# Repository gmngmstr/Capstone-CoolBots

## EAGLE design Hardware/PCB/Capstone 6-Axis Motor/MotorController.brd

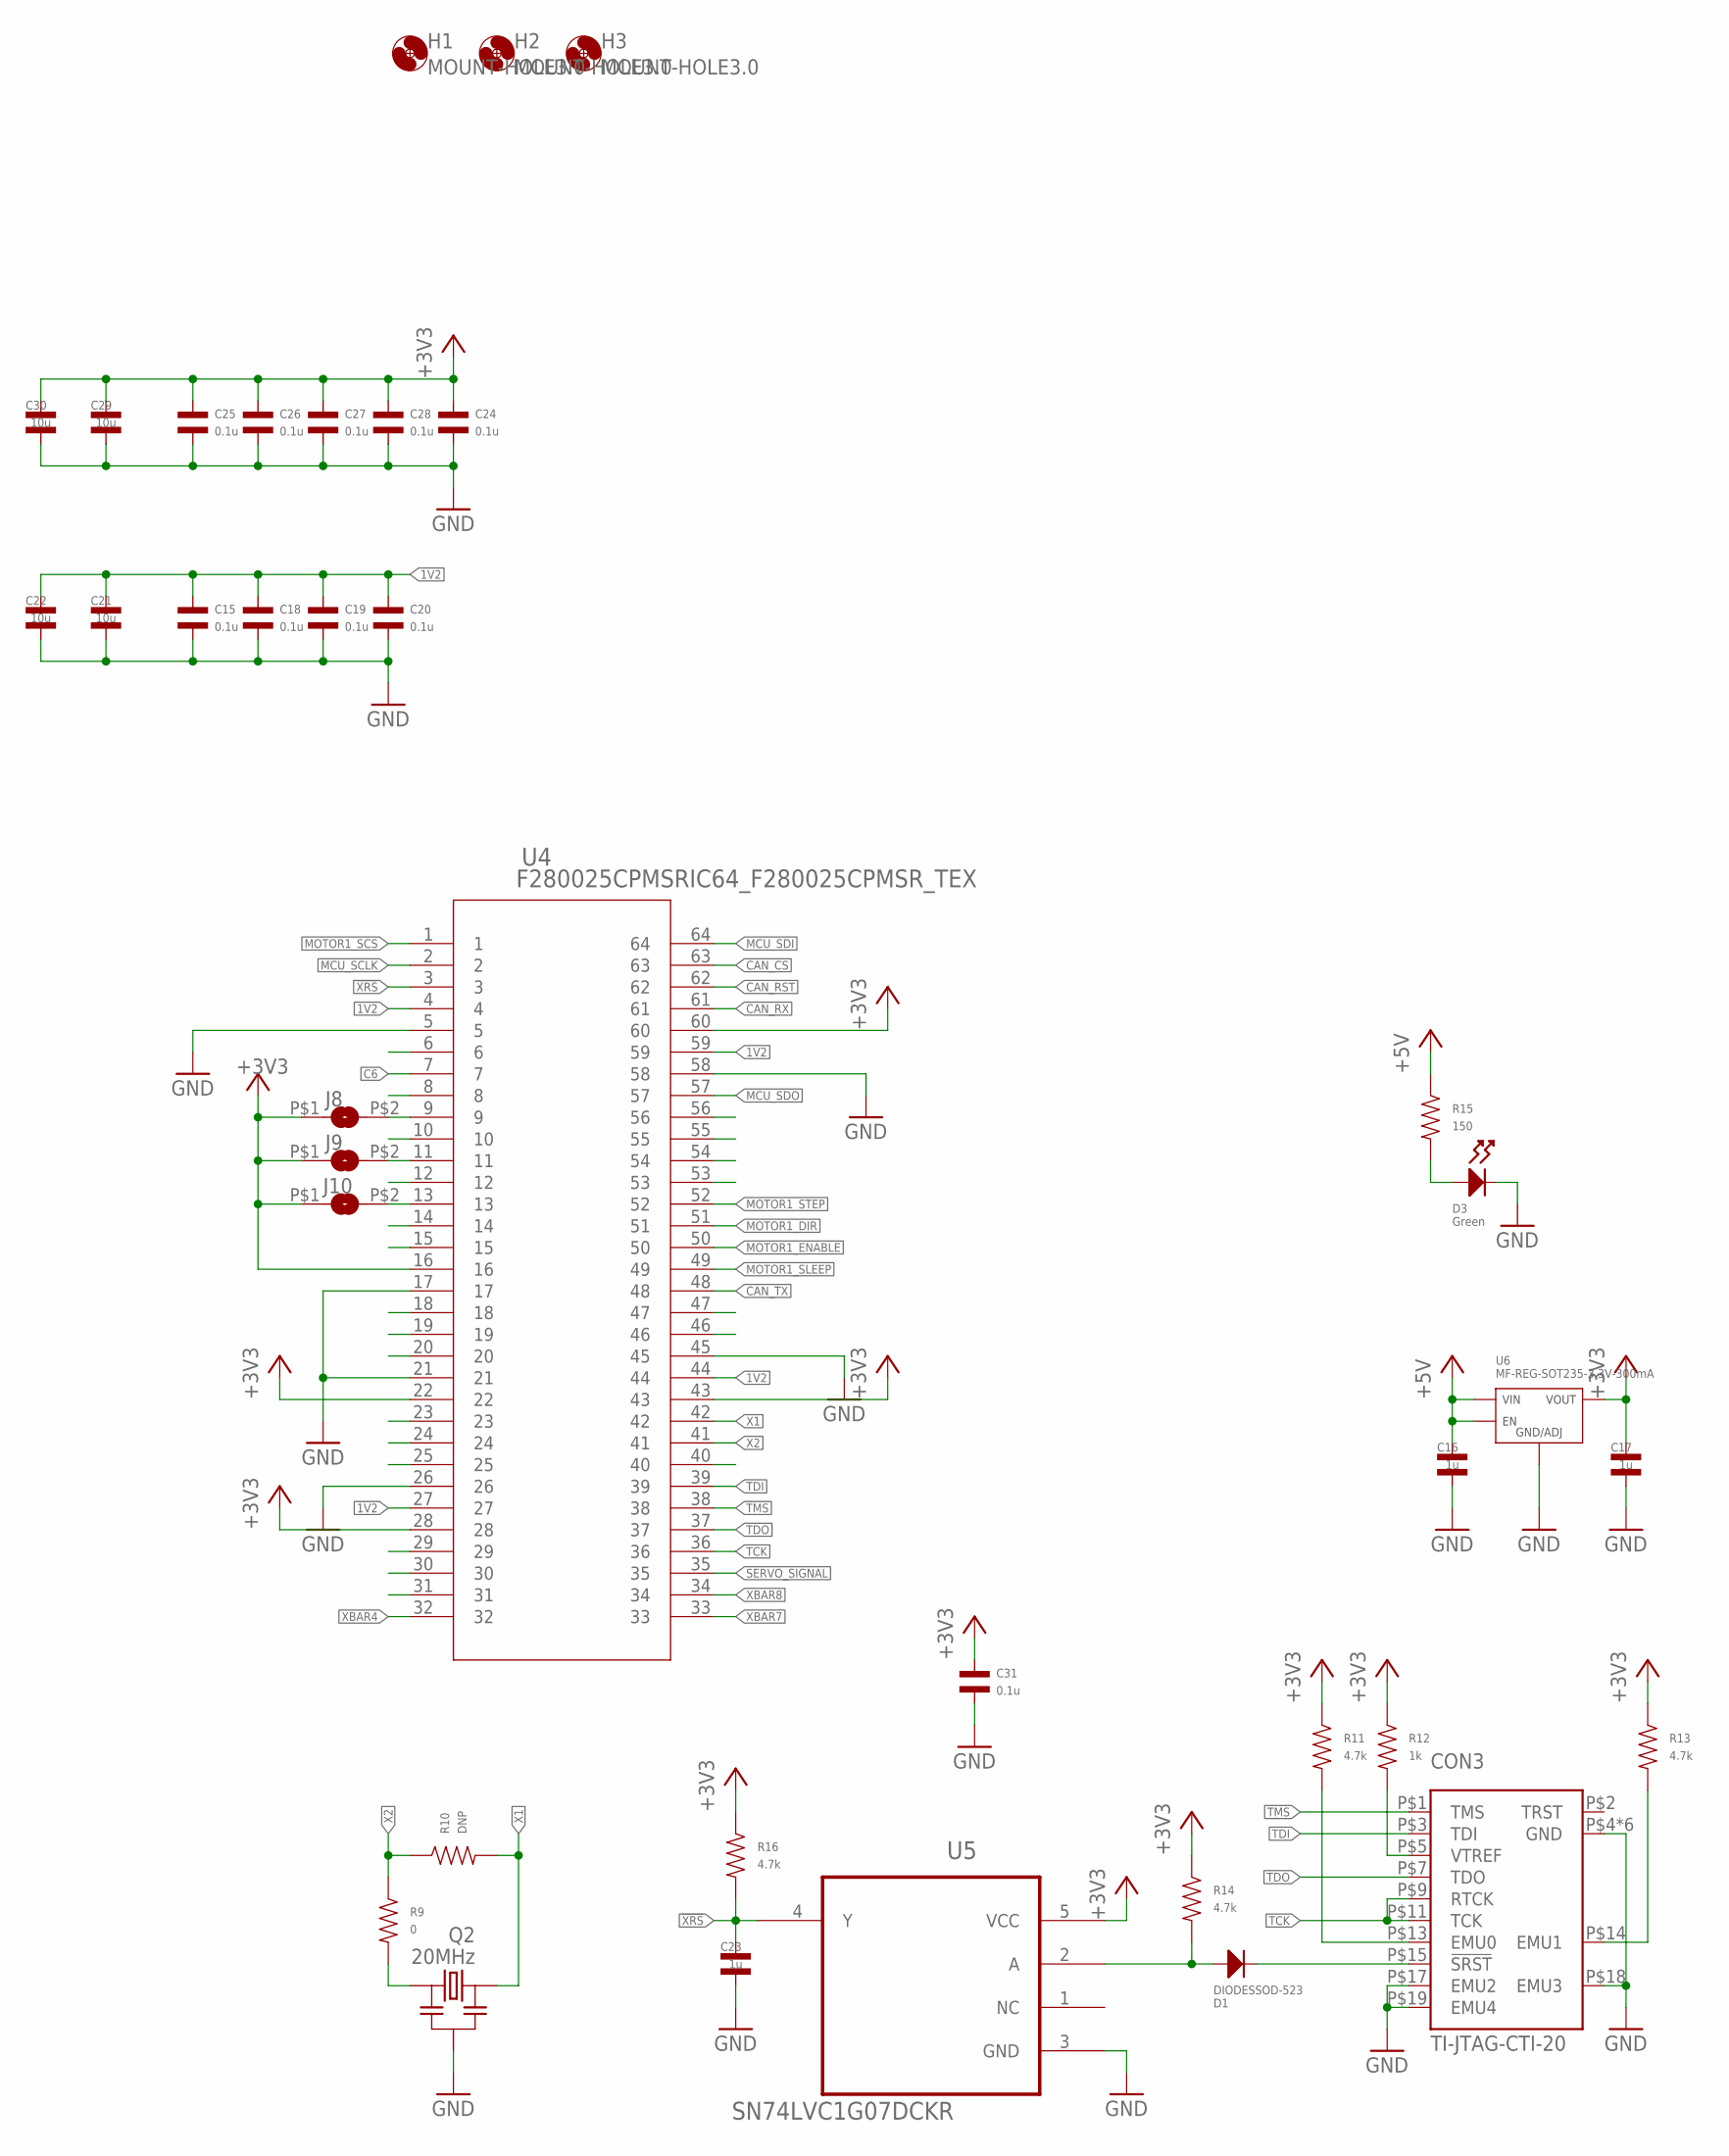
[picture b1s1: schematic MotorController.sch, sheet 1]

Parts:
C15, C18, C19, C20, C24, C25, C26, C27, C28, C31: 0.1u; C0402; MPN GCM155R71H104KE02D
C16, C17: 1u; C0805; MPN CL21B105KAFNNNE
C21, C22, C29, C30: 10u; C0805; MPN CL21A106KAYNNNE
C23: 1u; C0402; MPN CL05A105KA5NQNC
CON3: TI-JTAG-CTI-20; FTR-110-51-L-D-06; MPN FTR-110-51-L-D-06
D1: DIODESSOD-523; SOD523; MPN RB510SM-40FHT2R
D3: Green; LED0603; MPN SML-E12P8WT86
H1, H2, H3: MOUNT-HOLE3.0; 3,0
J8, J9, J10: JUMPER; SJ
Q2: 20MHz; CSTNE; MPN CSTNE20M0V53C000R0
R9: 0; R0402; MPN ERJ-2GE0R00X
R10: DNP; R0402
R11, R13, R14, R16: 4.7k; R0402; MPN ERJ-2RKF4701X
R12: 1k; R0402; MPN ERJ-2RKF1001X
R15: 150; R0805; MPN ERJ-6GEYJ151V
U4: F280025CPMSRIC64_F280025CPMSR_TEX; IC64_F280025CPMSR_TEX; MPN F280025CPMSR
U5: SN74LVC1G07DCKR; SOT65P210X110-5N
U6: MF-REG-SOT235-3.3V-300mA; SOT-23-5; MPN TLV70233PDBVR

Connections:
1V2: C15.P$1, C18.P$1, C19.P$1, C20.P$1, C21.P$1, C22.P$1, U4.4, U4.27, U4.44, U4.59
!XRS: C23.P$1, R16.P$2, U4.3, U5.4 (Y)
+3V3: C17.P$1, C24.P$1, C25.P$1, C26.P$1, C27.P$1, C28.P$1, C29.P$1, C30.P$1, C31.P$1, J8.P$1 (1), J9.P$1 (1), J10.P$1 (1), R11.P$1, R12.P$1, R13.P$1, R14.P$1, R16.P$1, U4.16, U4.22, U4.28, U4.43, U4.60, U5.5 (VCC), U6.P$5 (VOUT); also elsewhere on the board
+5V: C16.P$1, R15.P$1, U6.P$1 (VIN), U6.P$3 (EN); also elsewhere on the board
C6: U4.7; also elsewhere on the board
CAN_CS: U4.63; also elsewhere on the board
CAN_RST: U4.62; also elsewhere on the board
CAN_RX: U4.61; also elsewhere on the board
CAN_TX: U4.48; also elsewhere on the board
GND: C15.P$2, C16.P$2, C17.P$2, C18.P$2, C19.P$2, C20.P$2, C21.P$2, C22.P$2, C23.P$2, C24.P$2, C25.P$2, C26.P$2, C27.P$2, C28.P$2, C29.P$2, C30.P$2, C31.P$2, CON3.P$4 (GND), CON3.P$8 (GND), CON3.P$10 (GND), CON3.P$12 (GND), CON3.P$16 (GND), CON3.P$17 (EMU2), CON3.P$18 (EMU3), CON3.P$19 (EMU4), CON3.P$20 (GND), D3.CATHODE, Q2.2 (GND), U4.5, U4.17, U4.21, U4.26, U4.45, U4.58, U5.3 (GND), U6.P$2 (GND/ADJ); also elsewhere on the board
MCU_SCLK: U4.2; also elsewhere on the board
MCU_SDI: U4.64; also elsewhere on the board
MCU_SDO: U4.57; also elsewhere on the board
MOTOR1_DIR: U4.51; also elsewhere on the board
MOTOR1_ENABLE: U4.50; also elsewhere on the board
MOTOR1_SCS: U4.1; also elsewhere on the board
MOTOR1_SLEEP: U4.49; also elsewhere on the board
MOTOR1_STEP: U4.52; also elsewhere on the board
unnamed: D3.ANODE, R15.P$2
unnamed: CON3.P$5 (VTREF), R12.P$2
unnamed: Q2.3 (XOUT), R9.P$2
unnamed: CON3.P$13 (EMU0), R11.P$2
unnamed: CON3.P$14 (EMU1), R13.P$2
unnamed: CON3.P$15 (!SRST), D1.C (CATHODE)
unnamed: D1.A (ANODE), R14.P$2, U5.2 (A)
unnamed: J8.P$2 (2), U4.9
unnamed: J9.P$2 (2), U4.11
unnamed: J10.P$2 (2), U4.13
SERVO_SIGNAL: U4.35; also elsewhere on the board
TCK: CON3.P$9 (RTCK), CON3.P$11 (TCK), U4.36
TDI: CON3.P$3 (TDI), U4.39
TDO: CON3.P$7 (TDO), U4.37
TMS: CON3.P$1 (TMS), U4.38
X1: Q2.1 (XIN), R10.P$2, U4.42
X2: R9.P$1, R10.P$1, U4.41
XBAR4: U4.32; also elsewhere on the board
XBAR7: U4.33; also elsewhere on the board
XBAR8: U4.34; also elsewhere on the board

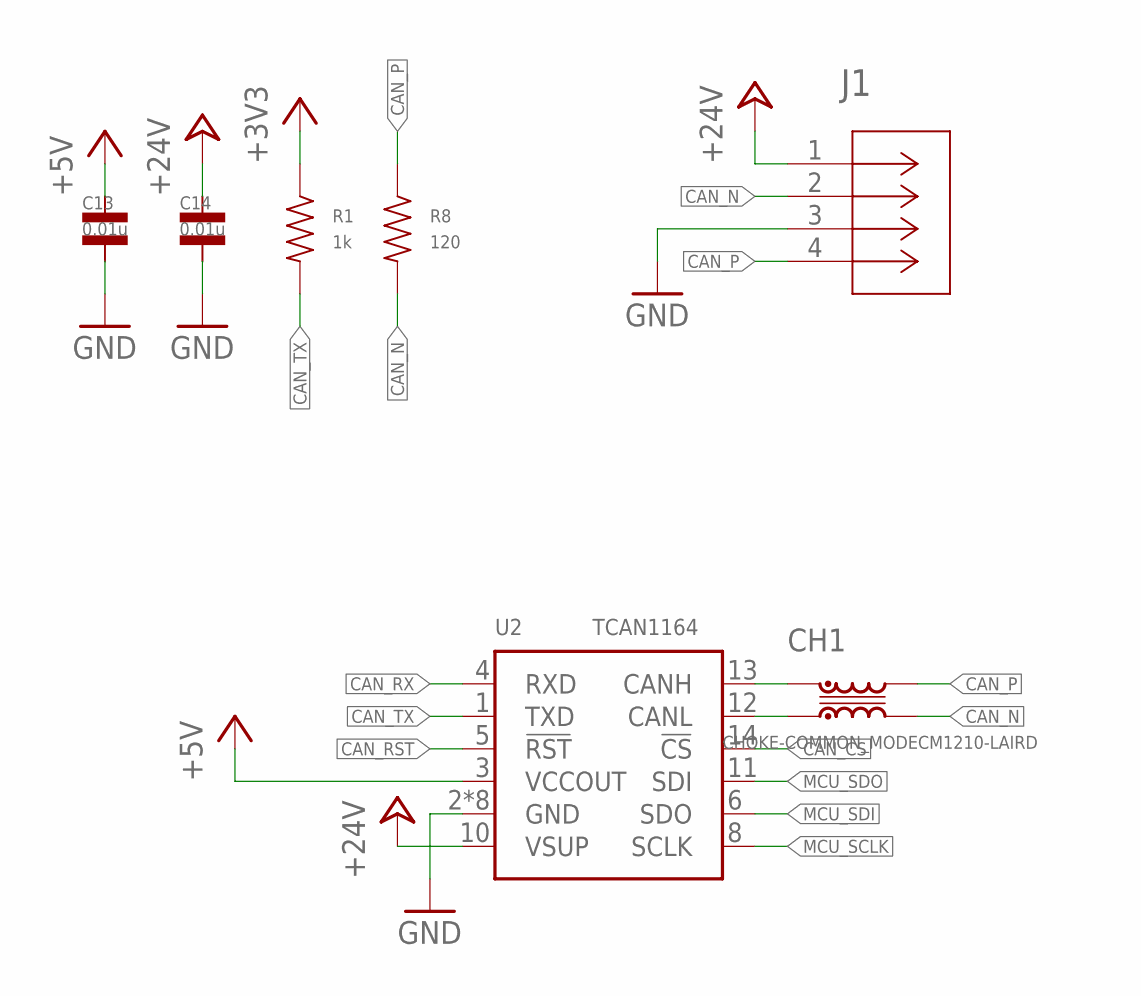
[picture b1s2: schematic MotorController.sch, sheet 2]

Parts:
C13, C14: 0.01u; C0402; MPN CL05B103KB5NNNC
CH1: CHOKE-COMMON_MODECM1210-LAIRD; CM1210-LAIRD; MPN CM1210B104R-1A
J1: 768250004CON_768250004_MOL; CON_768250004_MOL; MPN 0768250004
R1: 1k; R0402; MPN ERJ-2RKF1001X
R8: 120; R0402; MPN ERJ-2GEJ121X
U2: TCAN1164; CONV_TPS63021DSJ; MPN TCAN1164DMTRQ1

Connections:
+3V3: R1.P$1; also elsewhere on the board
+5V: C13.P$1, U2.3 (VCCOUT); also elsewhere on the board
+24V: C14.P$1, J1.1, U2.10 (VSUP); also elsewhere on the board
CAN_CS: U2.14 (!CS); also elsewhere on the board
CAN_N: CH1.P$3 (3), J1.2, R8.P$2
CAN_P: CH1.P$2 (2), J1.4, R8.P$1
CAN_RST: U2.5 (!RST); also elsewhere on the board
CAN_RX: U2.4 (RXD); also elsewhere on the board
CAN_TX: R1.P$2, U2.1 (TXD); also elsewhere on the board
GND: C13.P$2, C14.P$2, J1.3, U2.2 (GND), U2.15 (GND), U2.15_1 (GND), U2.15_2 (GND), U2.15_3 (GND), U2.15_4 (GND), U2.15_5 (GND), U2.15_6 (GND); also elsewhere on the board
MCU_SCLK: U2.8 (SCLK); also elsewhere on the board
MCU_SDI: U2.6 (SDO); also elsewhere on the board
MCU_SDO: U2.11 (SDI); also elsewhere on the board
unnamed: CH1.P$4 (4), U2.12 (CANL)
unnamed: CH1.P$1 (1), U2.13 (CANH)

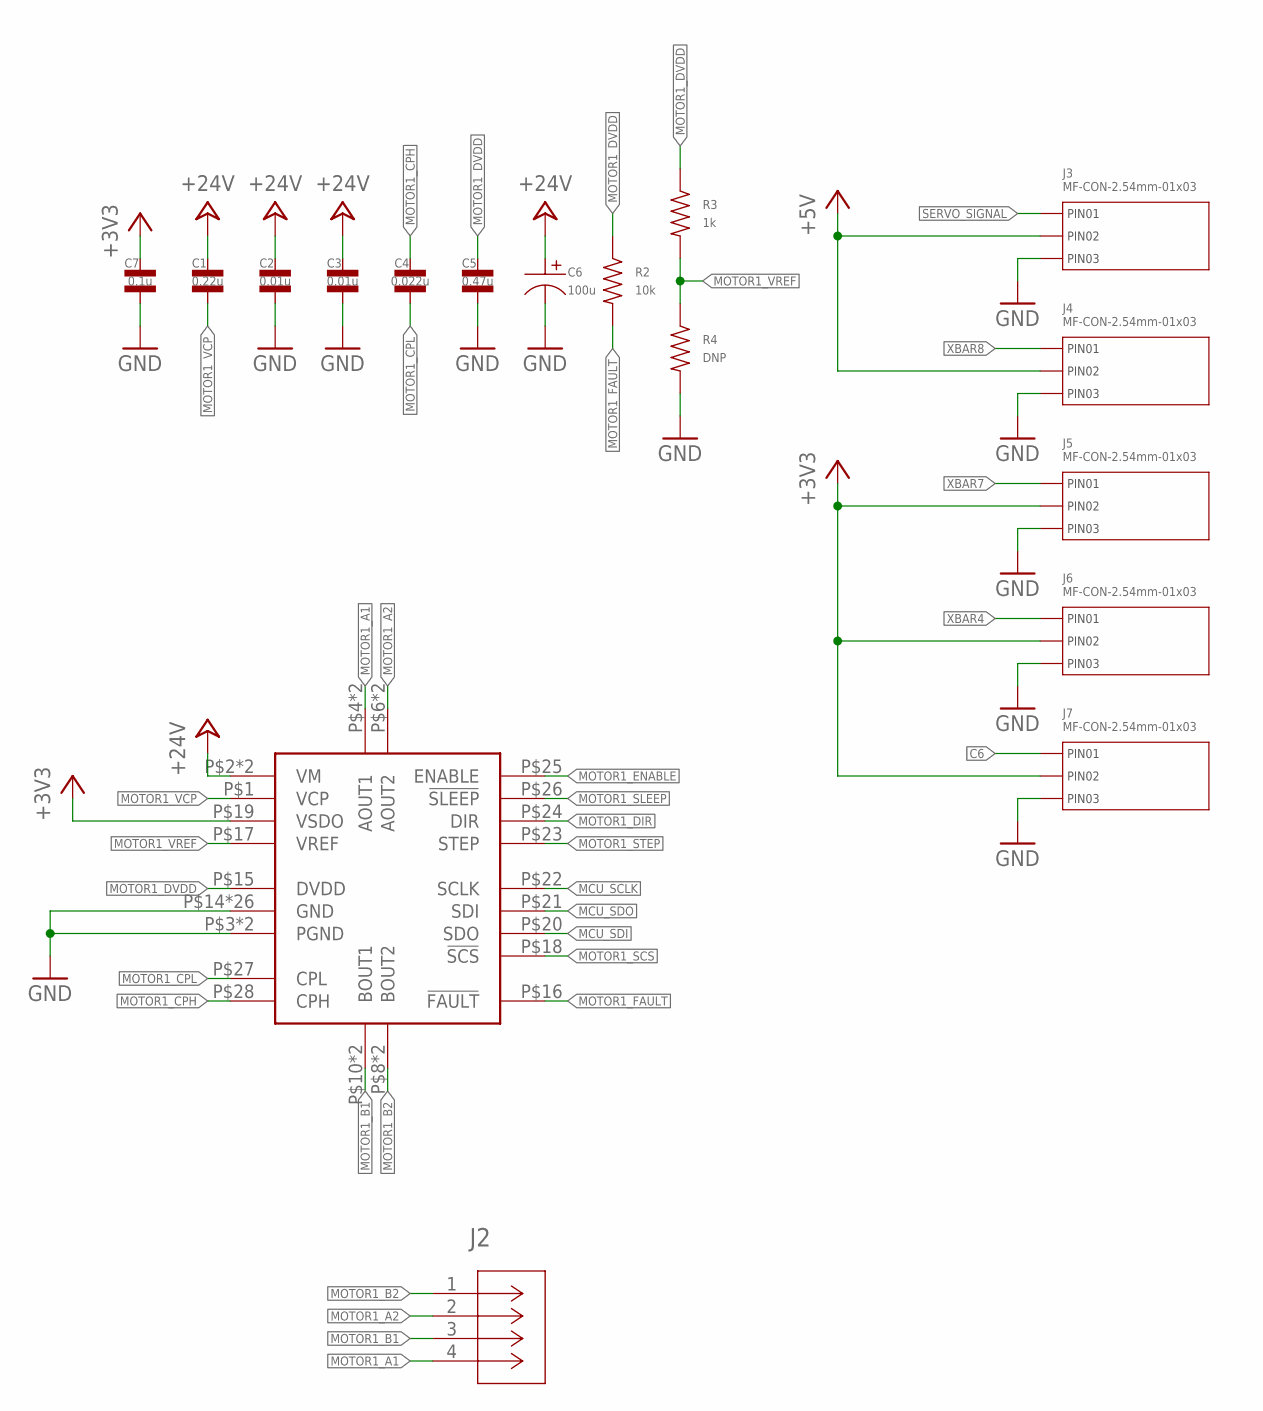
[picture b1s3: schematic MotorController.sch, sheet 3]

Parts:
C1: 0.22u; C0402; MPN CL05B224KA5VPNC
C2, C3: 0.01u; C0402; MPN CL05B103KB5NNNC
C4: 0.022u; C0402; MPN CL05B223KB5VPNC
C5: 0.47u; C0402; MPN CL05A474KA5NNNC
C6: 100u; CP6.3MM; MPN MAL218297603E3
C7: 0.1u; C0402; MPN GCM155R71H104KE02D
J2: 768250004CON_768250004_MOL; CON_768250004_MOL; MPN 0768250004
J3, J4, J5, J6, J7: MF-CON-2.54mm-01x03; PTH_2.54MM_01X03
R2: 10k; R0402; MPN ERJ-2RKF1002X
R3: 1k; R0402; MPN ERJ-2RKF1001X
R4: DNP; R0402
U1: DRV8434SPWPR; HTSSOP(PWP)-28; MPN DRV8434SPWPR

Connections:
+3V3: C7.P$1, J5.P$2 (PIN2), J6.P$2 (PIN2), J7.P$2 (PIN2), U1.P$19 (VSDO); also elsewhere on the board
+5V: J3.P$2 (PIN2), J4.P$2 (PIN2); also elsewhere on the board
+24V: C1.P$1, C2.P$1, C3.P$1, C6.P$1, U1.P$2 (VM), U1.P$13 (VM); also elsewhere on the board
C6: J7.P$1 (PIN1); also elsewhere on the board
GND: C2.P$2, C3.P$2, C5.P$2, C6.P$2, C7.P$2, J3.P$3 (PIN3), J4.P$3 (PIN3), J5.P$3 (PIN3), J6.P$3 (PIN3), J7.P$3 (PIN3), R4.P$2, U1.P$3 (PGND), U1.P$12 (PGND), U1.P$14 (GND), U1.P$29 (GND), U1.P$30 (GND), U1.P$31 (GND), U1.P$32 (GND), U1.P$33 (GND), U1.P$34 (GND), U1.P$35 (GND), U1.P$36 (GND), U1.P$37 (GND), U1.P$38 (GND), U1.P$39 (GND), U1.P$40 (GND), U1.P$41 (GND), U1.P$42 (GND), U1.P$43 (GND), U1.P$44 (GND), U1.P$45 (GND), U1.P$46 (GND), U1.P$47 (GND), U1.P$48 (GND), U1.P$49 (GND), U1.P$50 (GND), U1.P$51 (GND), U1.P$52 (GND), U1.P$53 (GND); also elsewhere on the board
MCU_SCLK: U1.P$22 (SCLK); also elsewhere on the board
MCU_SDI: U1.P$20 (SDO); also elsewhere on the board
MCU_SDO: U1.P$21 (SDI); also elsewhere on the board
MOTOR1_A1: J2.4, U1.P$4 (AOUT1), U1.P$5 (AOUT1)
MOTOR1_A2: J2.2, U1.P$6 (AOUT2), U1.P$7 (AOUT2)
MOTOR1_B1: J2.3, U1.P$10 (BOUT1), U1.P$11 (BOUT1)
MOTOR1_B2: J2.1, U1.P$8 (BOUT2), U1.P$9 (BOUT2)
MOTOR1_CPH: C4.P$1, U1.P$28 (CPH)
MOTOR1_CPL: C4.P$2, U1.P$27 (CPL)
MOTOR1_DIR: U1.P$24 (DIR); also elsewhere on the board
MOTOR1_DVDD: C5.P$1, R2.P$1, R3.P$1, U1.P$15 (DVDD)
MOTOR1_ENABLE: U1.P$25 (ENABLE); also elsewhere on the board
MOTOR1_FAULT: R2.P$2, U1.P$16 (!FAULT)
MOTOR1_SCS: U1.P$18 (!SCS); also elsewhere on the board
MOTOR1_SLEEP: U1.P$26 (!SLEEP); also elsewhere on the board
MOTOR1_STEP: U1.P$23 (STEP); also elsewhere on the board
MOTOR1_VCP: C1.P$2, U1.P$1 (VCP)
MOTOR1_VREF: R3.P$2, R4.P$1, U1.P$17 (VREF)
SERVO_SIGNAL: J3.P$1 (PIN1); also elsewhere on the board
XBAR4: J6.P$1 (PIN1); also elsewhere on the board
XBAR7: J5.P$1 (PIN1); also elsewhere on the board
XBAR8: J4.P$1 (PIN1); also elsewhere on the board

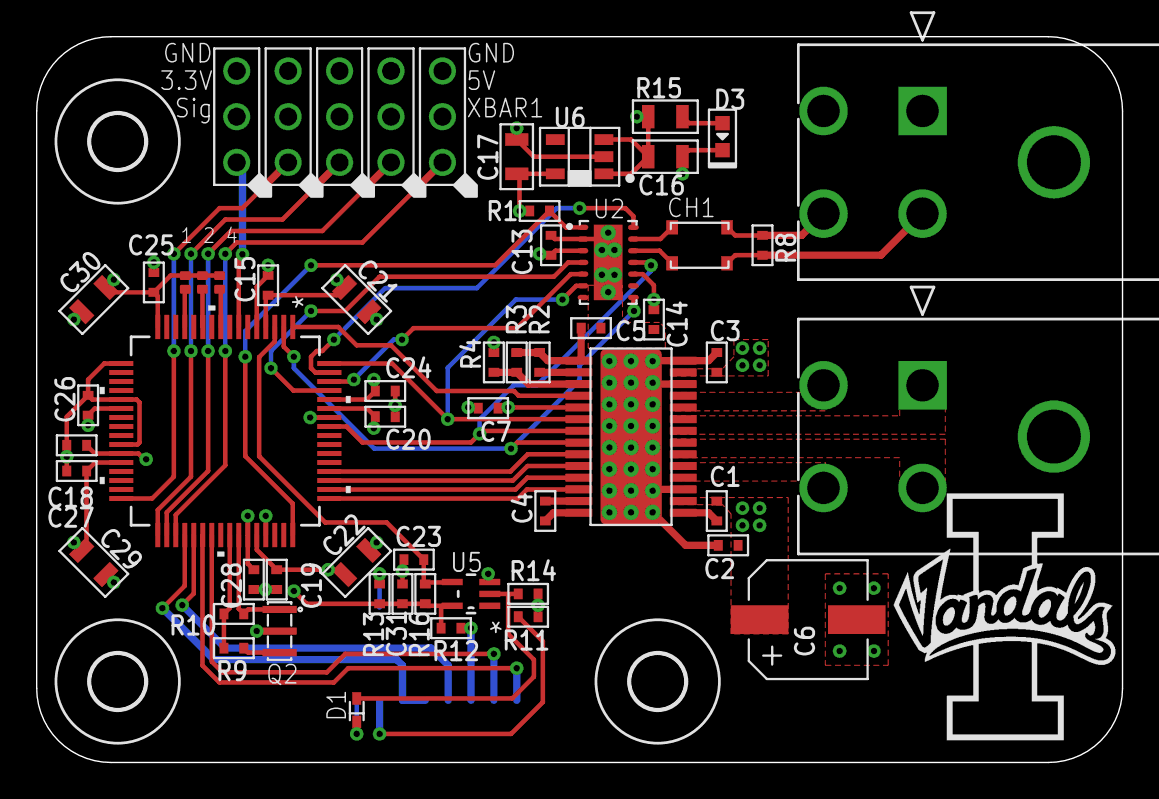
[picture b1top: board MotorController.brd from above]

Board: 4 copper layers, 60.3 x 40.3 mm, 62 parts (1 on the bottom side), 53 nets.

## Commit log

2024-11-23 Initial PCB Commit
2024-11-24 firmware commit
2024-11-24 Added temp files for folder composition
2024-11-28 Updated PCBs and added custom libraries
2024-12-10 updated device file
2024-12-10 Added SPI for the tcan module with some test code

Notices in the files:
parts and their libraries:
F280025CPMSR: COPYRIGHT: Copyright (C) 2024 Ultra Librarian. All rights reserved.
